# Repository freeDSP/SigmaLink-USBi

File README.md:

# SigmaLink USBi

The SigmaLink USBi is an all-in-one real-time programming interface.

MAIN COORDINATOR: [Max Chan](https://github.com/xcvista)

The SigmaLink USBi is a low-budget real-time programming device for the freeDSP and other DSP boards from Analog Devices. It is a new PCB design based on a CY7C68013 chip.

It has the same features as the Analog Devices USB interface (EVAL-ADUSB2EBZ), such as changing parameters while already using the freeDSP or easy changes of the schematic in SigmaStudio. You also can write your program to the EEPROM.

Please refer to the documentation for more information:

[Google Doc](https://docs.google.com/document/d/13BDac6Mss2I0CBOsSrk4YG-c8GQUpgU41vkwsMnYBss/edit?usp=sharing)

## License

This work and all other materials under https://github.com/freeDSP are licensed under a [Creative Commons Attribution Share-Alike 4.0 license](LICENSE.md). This allows for both personal and commercial derivative works, as long as they credit freeDSP and release their designs under the same license.

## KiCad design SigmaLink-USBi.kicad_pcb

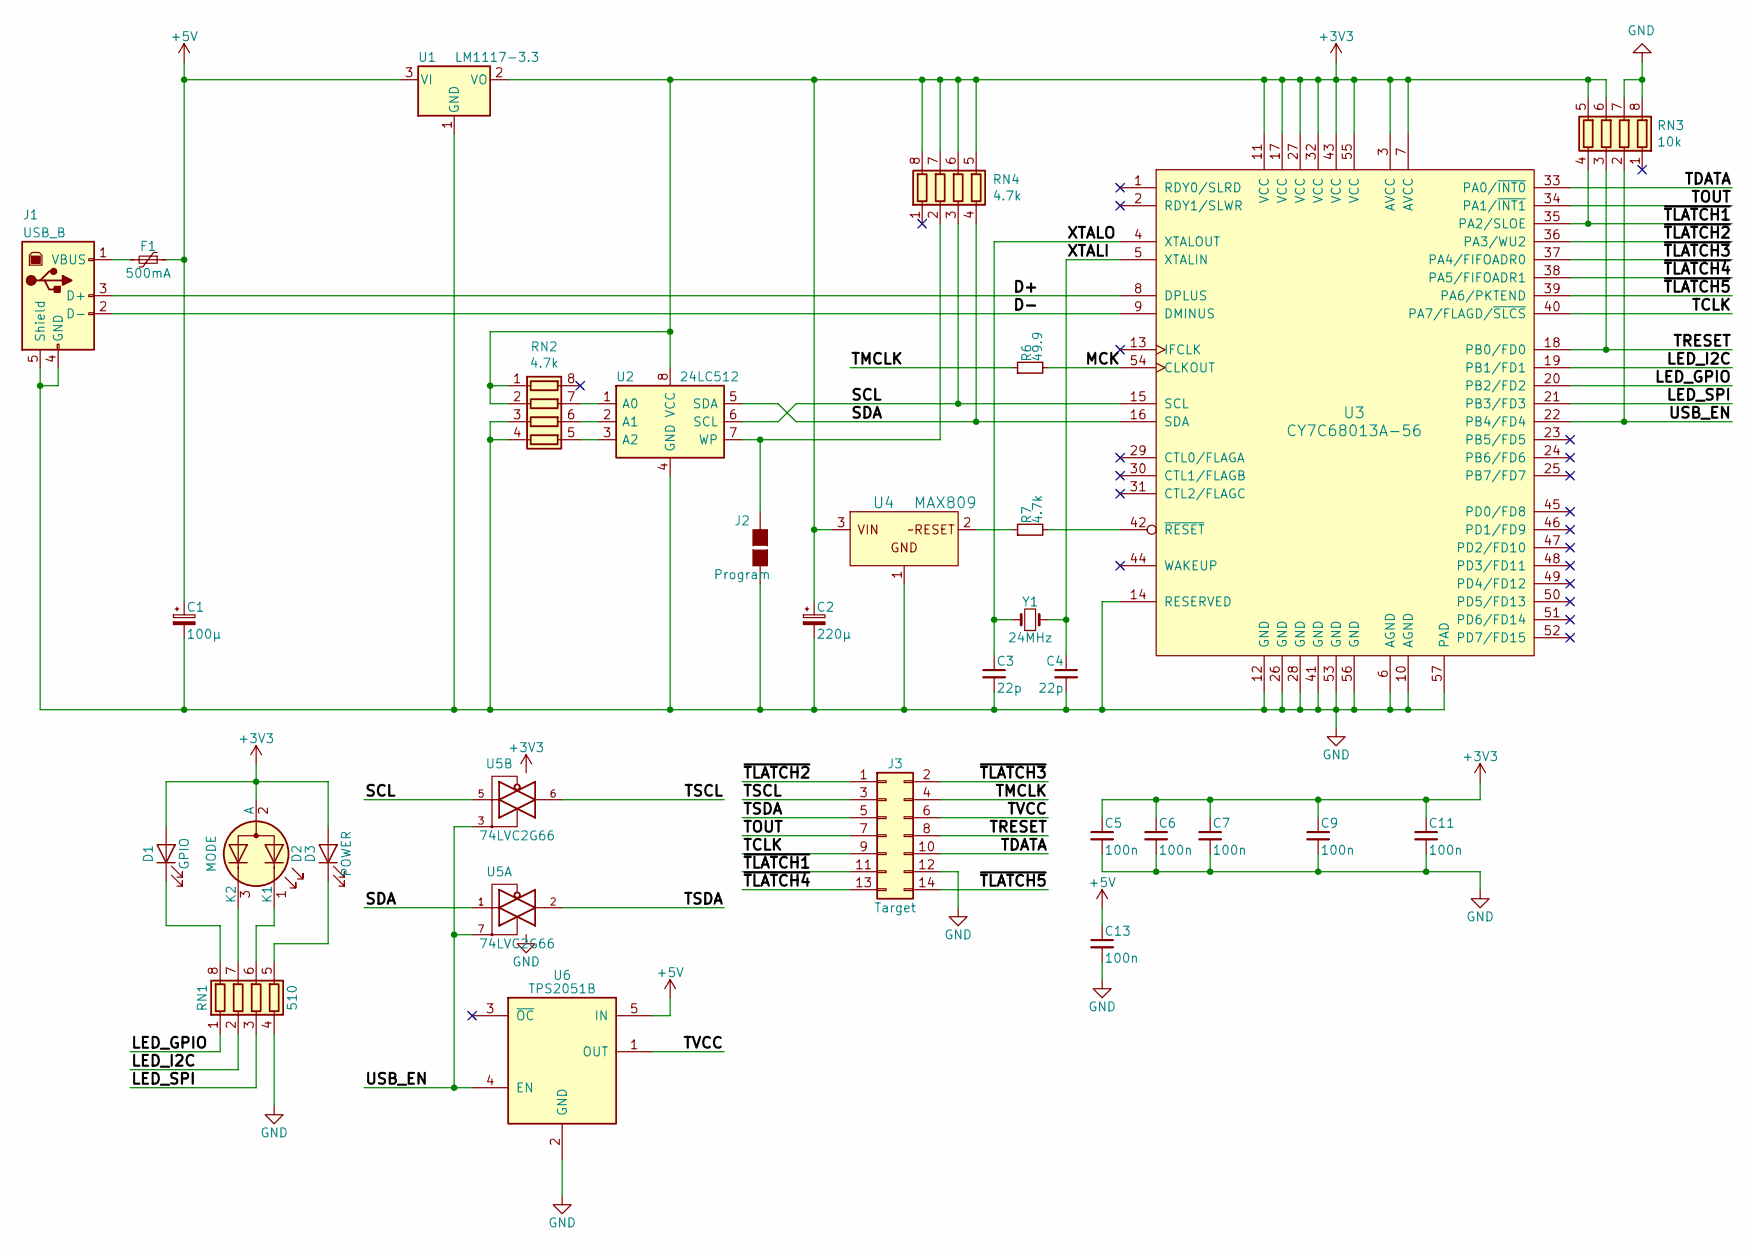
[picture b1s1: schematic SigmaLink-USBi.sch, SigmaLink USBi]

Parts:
C1: 100µ; CP_Elec_6.3x5.3
C2: 220µ; CP_Elec_6.3x5.3
C3, C4: 22p; C_0603_1608Metric_Pad1.05x0.95mm_HandSolder
C5, C6, C7, C9, C11, C13: 100n; C_0603_1608Metric_Pad1.05x0.95mm_HandSolder
D1: GPIO; LED_D3.0mm
D2: MODE; LED_D3.0mm-3
D3: POWER; LED_D3.0mm
F1: 500mA; Fuse_1812_4532Metric_Pad1.30x3.40mm_HandSolder
J1: USB_B; USB_B_OST_USB-B1HSxx_Horizontal
J2: Program; PinHeader_2x01_P1.27mm_Vertical
J3: Target; IDC-Header_2x07_P2.54mm_Horizontal
R6: 49.9; R_0603_1608Metric_Pad1.05x0.95mm_HandSolder
R7: 4.7k; R_0603_1608Metric_Pad1.05x0.95mm_HandSolder
RN1: 510; R_Array_Convex_4x0603
RN2, RN4: 4.7k; R_Array_Convex_4x0603
RN3: 10k; R_Array_Convex_4x0603
U1: LM1117-3.3; SOT-223-3_TabPin2
U2: 24LC512; SOIC-8_3.9x4.9mm_P1.27mm
U3: CY7C68013A-56; QFN-56-1EP_8x8mm_P0.5mm_EP4.6x5.3mm
U4: MAX809; SOT-23
U5: 74LVC2G66; VSSOP-8_3.0x3.0mm_P0.65mm
U6: TPS2051B; SOT-23-5
Y1: 24MHz; Crystal_SMD_5032-2Pin_5.0x3.2mm

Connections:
+5V: C1.1, C13.1, F1.1, U1.3 (VI), U6.5 (IN)
/D+: J1.3 (D+), U3.8 (DPLUS)
/D-: J1.2 (D-), U3.9 (DMINUS)
/LED_GPIO: RN1.1 (R1.1), U3.20 (PB2/FD2)
/LED_I2C: RN1.2 (R2.1), U3.19 (PB1/FD1)
/LED_SPI: RN1.3 (R3.1), U3.21 (PB3/FD3)
/MCK: R6.2, U3.54 (CLKOUT)
/SCL: RN4.3 (R3.1), U2.6 (SCL), U3.15 (SCL), U5.5
/SDA: RN4.4 (R4.1), U2.5 (SDA), U3.16 (SDA), U5.1
/TCLK: J3.9, U3.40 (PA7/FLAGD/~SLCS)
/TDATA: J3.10, U3.33 (PA0/~INT0)
/TMCLK: J3.4, R6.1
/TOUT: J3.7, U3.34 (PA1/~INT1)
/TRESET: J3.8, RN3.3 (R3.1), U3.18 (PB0/FD0)
/TSCL: J3.3, U5.6
/TSDA: J3.5, U5.2
/TVCC: J3.6, U6.1 (OUT)
/USB_EN: RN3.2 (R2.1), U3.22 (PB4/FD4), U5.3, U5.7, U6.4 (EN)
/XTALI: C4.1, U3.5 (XTALIN), Y1.2
/XTALO: C3.1, U3.4 (XTALOUT), Y1.1
/~TLATCH1: J3.11, RN3.4 (R4.1), U3.35 (PA2/SLOE)
/~TLATCH2: J3.1, U3.36 (PA3/WU2)
/~TLATCH3: J3.2, U3.37 (PA4/FIFOADR0)
/~TLATCH4: J3.13, U3.38 (PA5/FIFOADR1)
/~TLATCH5: J3.14, U3.39 (PA6/PKTEND)
GND: C1.2, C2.2, C3.2, C4.2, C5.2, C6.2, C7.2, C9.2, C11.2, C13.2, J1.4 (GND), J1.5 (Shield), J2.2 (G2), J3.12, RN1.4 (R4.1), RN2.3 (R3.1), RN2.4 (R4.1), RN3.7 (R2.2), RN3.8 (R1.2), U1.1 (GND), U2.4 (GND), U3.6 (AGND), U3.10 (AGND), U3.12 (GND), U3.14 (RESERVED), U3.26 (GND), U3.28 (GND), U3.41 (GND), U3.53 (GND), U3.56 (GND), U3.57 (PAD), U4.1 (GND), U5.4 (GND), U6.2 (GND)
unnamed: D1.1 (K), RN1.8 (R1.2)
unnamed: D2.1 (K1), RN1.6 (R3.2)
unnamed: D2.3 (K2), RN1.7 (R2.2)
unnamed: D3.1 (K), RN1.5 (R4.2)
unnamed: F1.2, J1.1 (VBUS)
unnamed: J2.1 (G1), RN4.2 (R2.1), U2.7 (WP)
unnamed: R7.1, U4.2 (~RESET)
unnamed: R7.2, U3.42 (~RESET)
unnamed: RN2.5 (R4.2), U2.3 (A2)
unnamed: RN2.6 (R3.2), U2.2 (A1)
unnamed: RN2.7 (R2.2), U2.1 (A0)

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
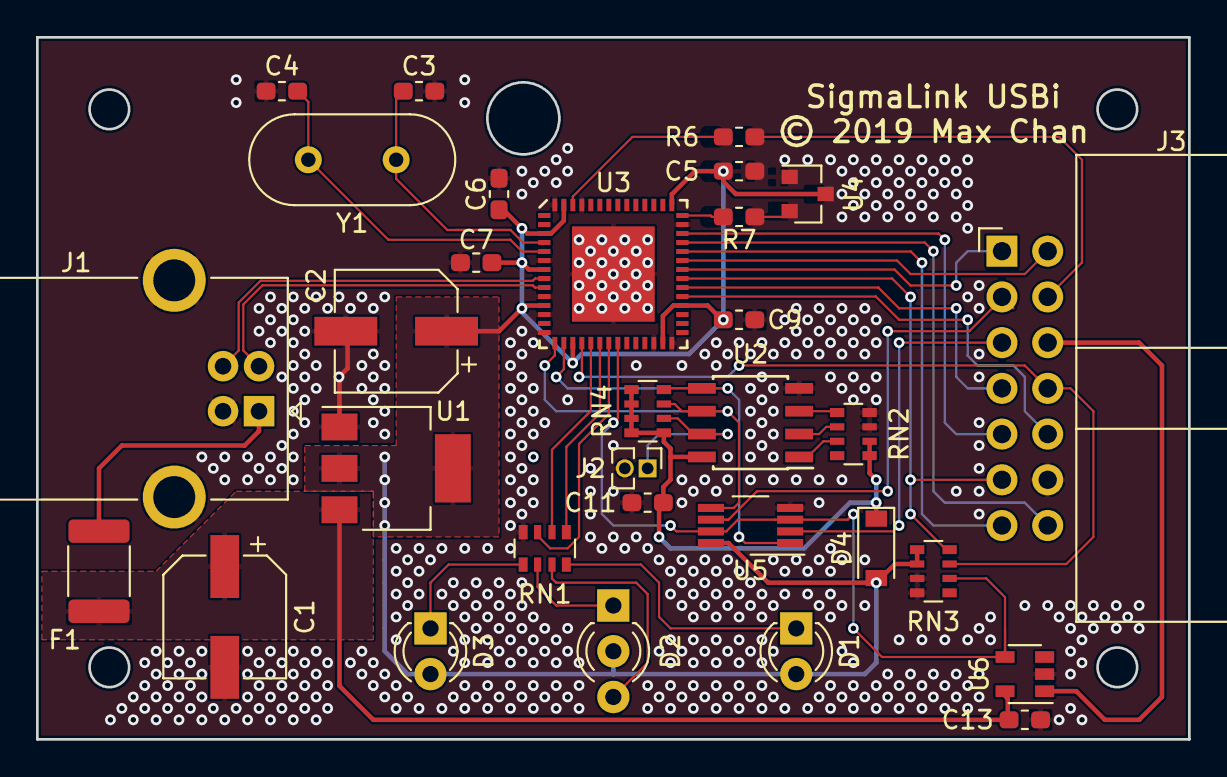
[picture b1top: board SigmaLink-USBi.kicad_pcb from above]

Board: 2 copper layers, 64.0 x 39.0 mm, 31 parts (0 on the bottom side), 39 nets.

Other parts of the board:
D4: B5819W; D_SOD-123

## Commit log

2018-05-30 Bulk importing SigmaLink USBi source files
2018-05-30 Introduced documentations
2018-05-30 I need pictures illustrating my point.
2018-05-30 I need pictures illustrating my point. Part 2
2018-05-30 Adding the schematics as Docs
2018-05-30 Starting: firmware conversion tool.
2018-05-30 Finished: txt2bin.c
2018-06-08 added link to Google documentation
2018-10-08 Preparing for v1r2
2018-10-08 Rerouted the board
2018-10-08 Peparing release: v2r1
2018-10-08 Touchup: NoConn's
2019-04-26 Resistor packs are used more extensively.
    Also a re-layout.
2019-04-26 Update SigmaLink-USBi.sch
    Update version number.
2019-04-26 Timestamp change?
2019-12-08 General maintanence commit.

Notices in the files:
SigmaLink-USBi.kicad_pcb:
© 2019 Max Chan
